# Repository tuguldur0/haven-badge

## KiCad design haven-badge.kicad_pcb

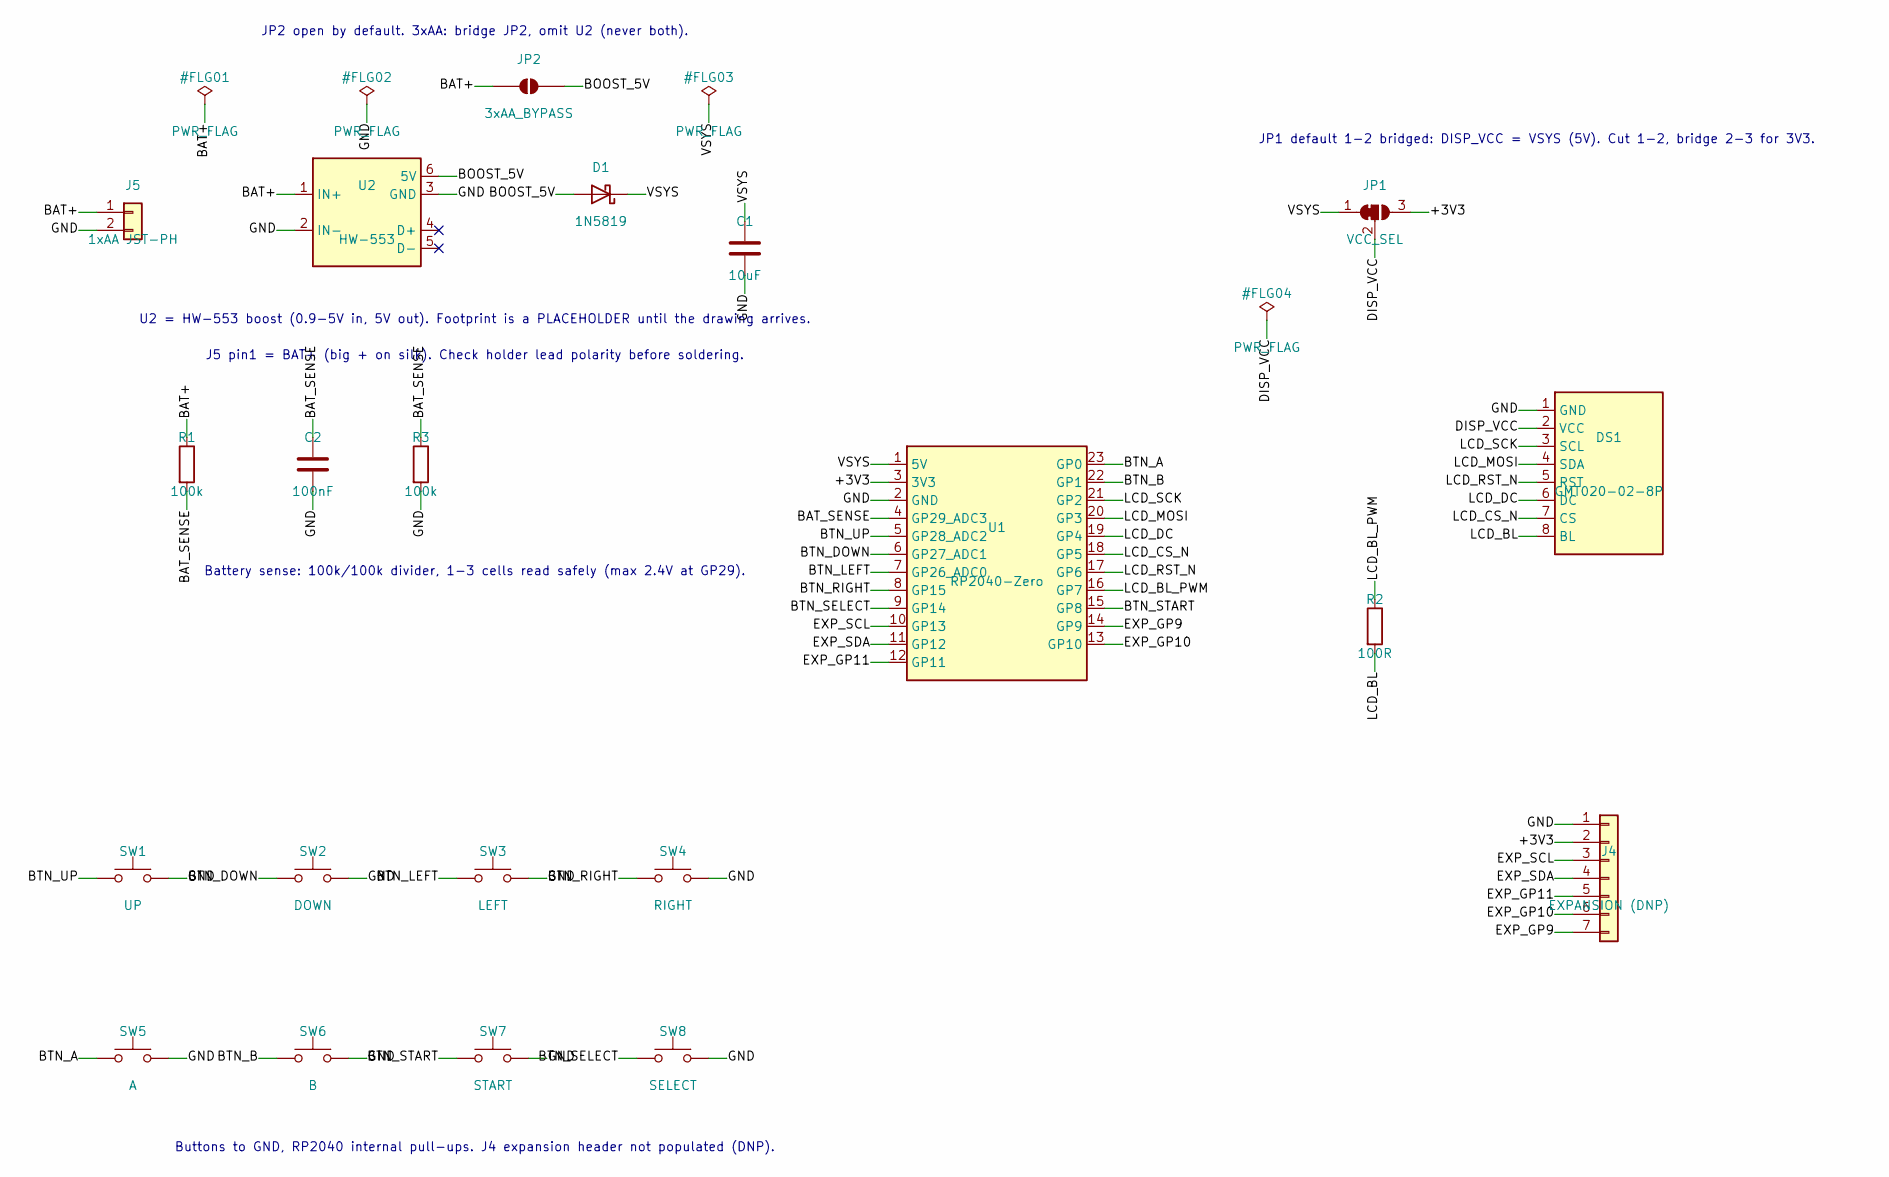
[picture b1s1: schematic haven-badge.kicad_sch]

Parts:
C1: 10uF; C_Disc_D5.0mm_W2.5mm_P5.00mm
C2: 100nF; C_Disc_D5.0mm_W2.5mm_P5.00mm
D1: 1N5819; D_DO-41_SOD81_P10.16mm_Horizontal
DS1: GMT020-02-8P; GMT020-02-8P_Socketed
J4: EXPANSION (DNP); PinHeader_1x07_P2.54mm_Vertical
J5: 1xAA JST-PH; JST_PH_B2B-PH-K_1x02_P2.00mm_Vertical
JP1: VCC_SEL; SolderJumper-3_P1.3mm_Bridged12_RoundedPad1.0x1.5mm_NumberL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
JP2: 3xAA_BYPASS; SolderJumper-2_P1.3mm_Open_RoundedPad1.0x1.5mm
R1, R3: 100k; R_Axial_DIN0207_L6.3mm_D2.5mm_P10.16mm_Horizontal
R2: 100R; R_Axial_DIN0207_L6.3mm_D2.5mm_P10.16mm_Horizontal
SW1: UP; SW_PUSH_6mm
SW2: DOWN; SW_PUSH_6mm
SW3: LEFT; SW_PUSH_6mm
SW4: RIGHT; SW_PUSH_6mm
SW5: A; SW_PUSH_6mm
SW6: B; SW_PUSH_6mm
SW7: START; SW_PUSH_6mm
SW8: SELECT; SW_PUSH_6mm
U1: RP2040-Zero; RP2040-Zero_Socketed
U2: HW-553; HW-553_Placeholder

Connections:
/+3V3: J4.2, JP1.3 (B), U1.3 (3V3)
/BAT+: J5.1, JP2.1 (A), R1.1, U2.1 (IN+)
/BAT_SENSE: C2.1, R1.2, R3.1, U1.4 (GP29_ADC3)
/BOOST_5V: D1.2 (A), JP2.2 (B), U2.6 (5V)
/BTN_A: SW5.1, U1.23 (GP0)
/BTN_B: SW6.1, U1.22 (GP1)
/BTN_DOWN: SW2.1, U1.6 (GP27_ADC1)
/BTN_LEFT: SW3.1, U1.7 (GP26_ADC0)
/BTN_RIGHT: SW4.1, U1.8 (GP15)
/BTN_SELECT: SW8.1, U1.9 (GP14)
/BTN_START: SW7.1, U1.15 (GP8)
/BTN_UP: SW1.1, U1.5 (GP28_ADC2)
/DISP_VCC: DS1.2 (VCC), JP1.2 (C)
/EXP_GP9: J4.7, U1.14 (GP9)
/EXP_GP10: J4.6, U1.13 (GP10)
/EXP_GP11: J4.5, U1.12 (GP11)
/EXP_SCL: J4.3, U1.10 (GP13)
/EXP_SDA: J4.4, U1.11 (GP12)
/GND: C1.2, C2.2, DS1.1 (GND), J4.1, J5.2, R3.2, SW1.2, SW2.2, SW3.2, SW4.2, SW5.2, SW6.2, SW7.2, SW8.2, U1.2 (GND), U2.2 (IN-), U2.3 (GND)
/LCD_BL: DS1.8 (BL), R2.2
/LCD_BL_PWM: R2.1, U1.16 (GP7)
/LCD_CS_N: DS1.7 (CS), U1.18 (GP5)
/LCD_DC: DS1.6 (DC), U1.19 (GP4)
/LCD_MOSI: DS1.4 (SDA), U1.20 (GP3)
/LCD_RST_N: DS1.5 (RST), U1.17 (GP6)
/LCD_SCK: DS1.3 (SCL), U1.21 (GP2)
/VSYS: C1.1, D1.1 (K), JP1.1 (A), U1.1 (5V)

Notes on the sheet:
U2 = HW-553 boost (0.9-5V in, 5V out). Footprint is a PLACEHOLDER until the drawing arrives.
J5 pin1 = BAT+ (big + on silk). Check holder lead polarity before soldering.
JP2 open by default. 3xAA: bridge JP2, omit U2 (never both).
Battery sense: 100k/100k divider, 1-3 cells read safely (max 2.4V at GP29).
Buttons to GND, RP2040 internal pull-ups. J4 expansion header not populated (DNP).
JP1 default 1-2 bridged: DISP_VCC = VSYS (5V). Cut 1-2, bridge 2-3 for 3V3.

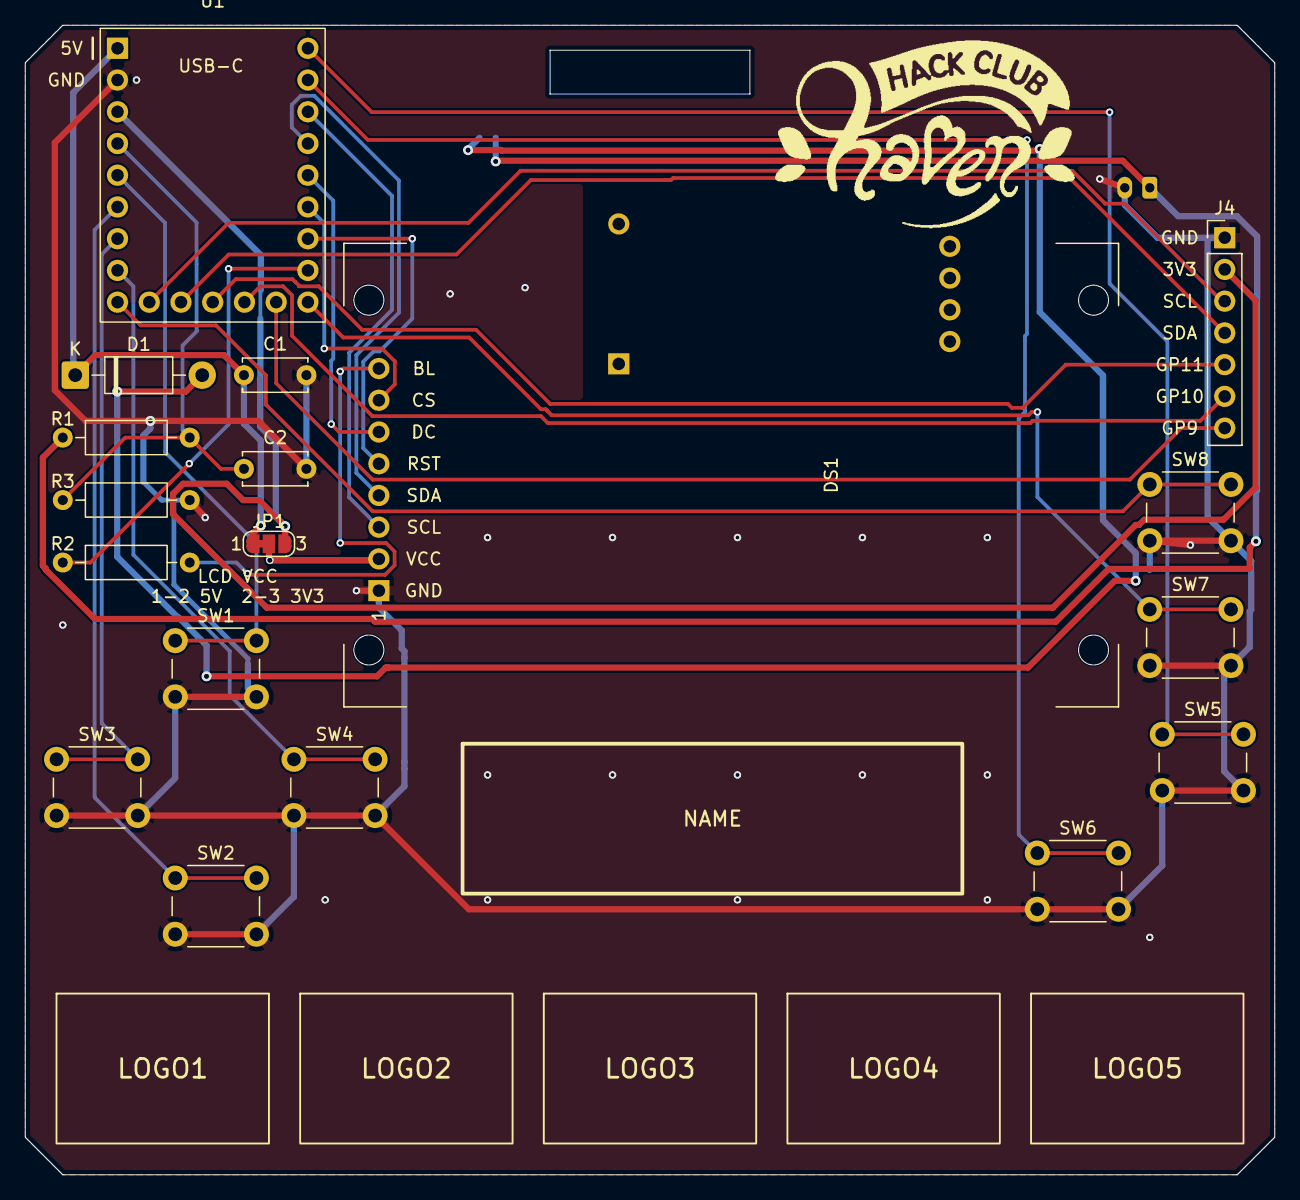
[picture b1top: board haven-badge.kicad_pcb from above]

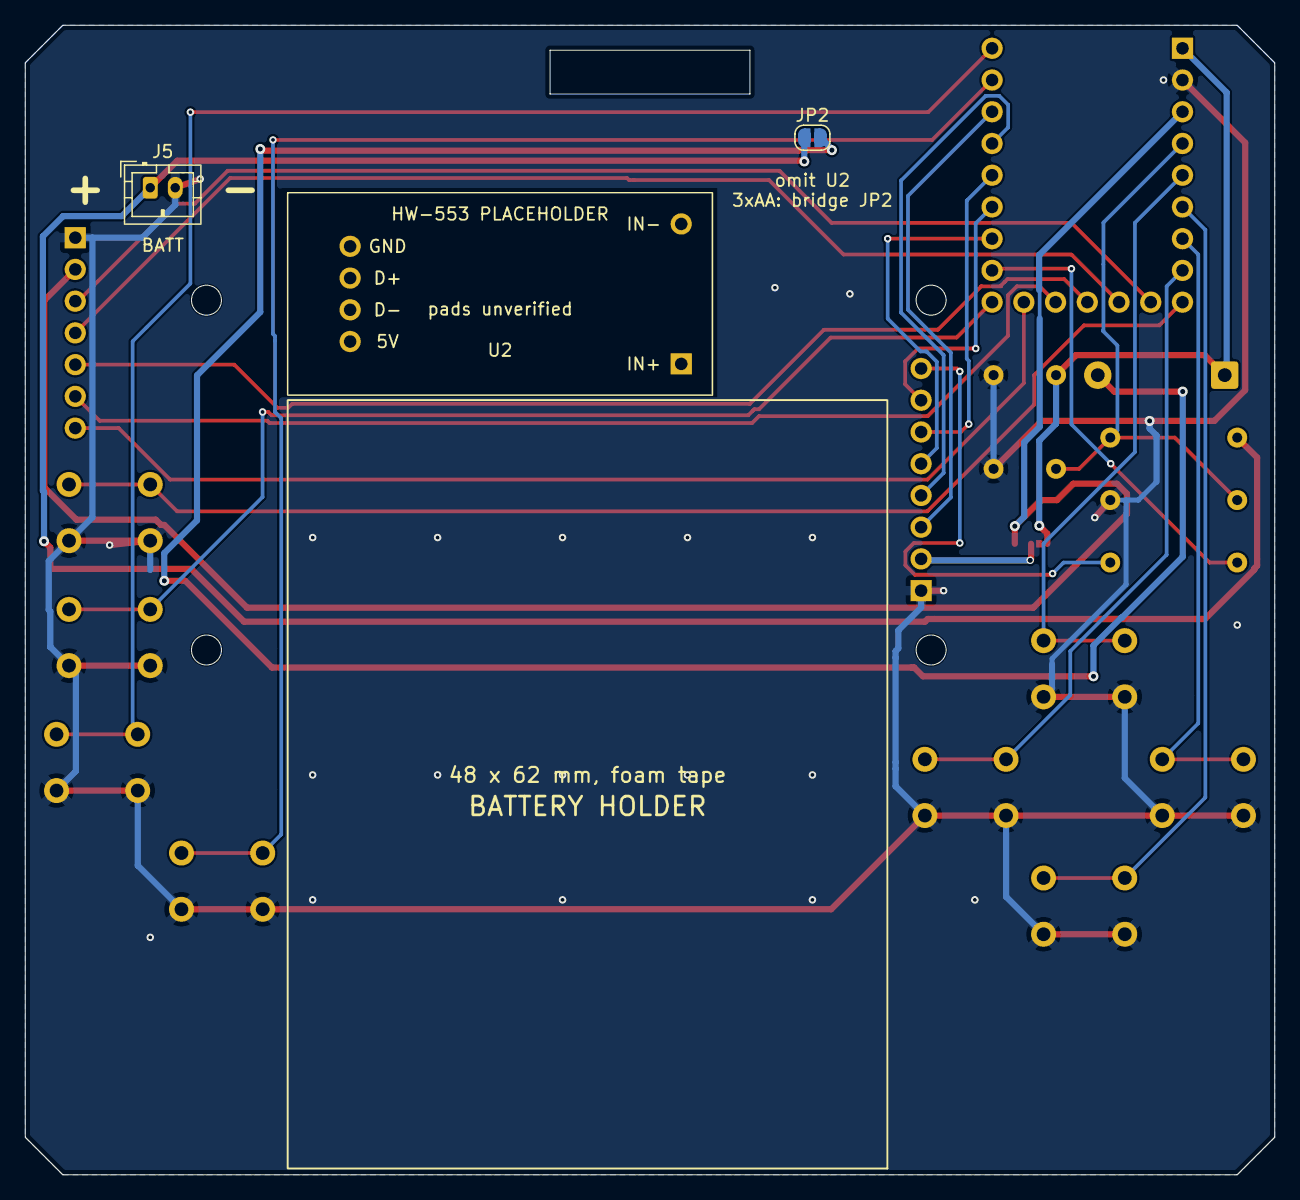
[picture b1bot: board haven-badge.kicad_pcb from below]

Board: 2 copper layers, 100.0 x 92.0 mm, 29 parts (6 on the bottom side), 27 nets.

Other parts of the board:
G1: Haven_Logo
G2: Name_Box
G3: Polarity_PH2
G4: J4_Labels
G5: JP2_Label
G6: JP1_Label
G7: Holder_Reserve
G8: Logo_Strip
